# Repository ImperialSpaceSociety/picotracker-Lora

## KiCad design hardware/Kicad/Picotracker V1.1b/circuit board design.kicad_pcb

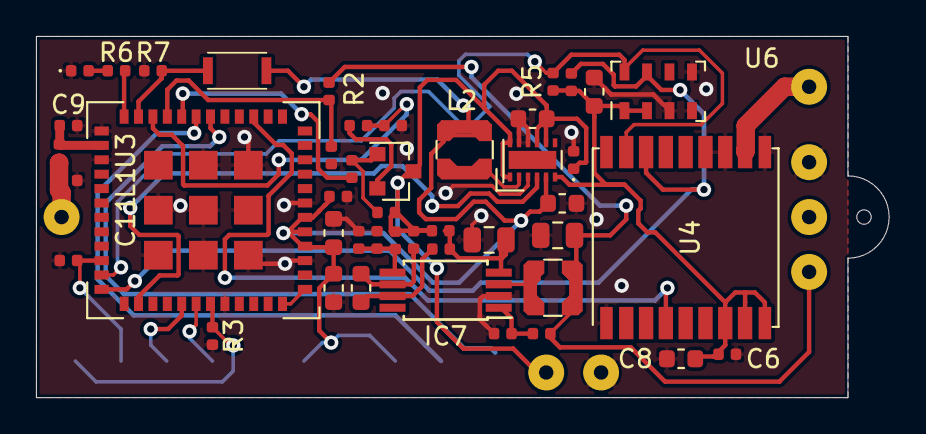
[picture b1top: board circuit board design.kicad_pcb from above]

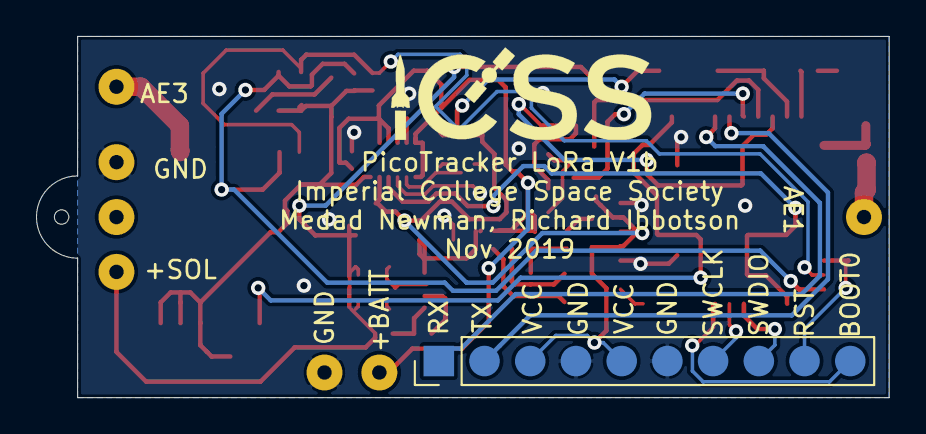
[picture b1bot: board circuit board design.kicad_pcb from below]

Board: 2 copper layers, 47.4 x 20.1 mm, 55 parts (8 on the bottom side), 34 nets.

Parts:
AE1: Lora Antenna; SolderWirePad_1x01_Drill0.8mm
AE3: GPS Antenna; SolderWirePad_1x01_Drill0.8mm
C1, C5, C6, C13: 100nF; C_0402_1005Metric
C2, C8, C10, C12: 10uF; C_0603_1608Metric
C3: 4.7uF; C_0805_2012Metric
C4, C16: 1nF; C_0402_1005Metric
C7, C15: 1uF; C_0603_1608Metric
C9, C11: NF; C_0402_1005Metric
C14: 220nF; C_0603_1608Metric
C17: 22uF; C_0805_2012Metric
D1: LED; LED_0402_1005Metric
D2: D_Schottky; D_0402_1005Metric
IC7: SPV1040; TSSOP-8_4.4x3mm_P0.65mm
J1: Conn_01x10; 10Pad
J2: GND; SolderWirePad_1x01_Drill0.8mm
J3: +SOL; SolderWirePad_1x01_Drill0.8mm
J4: BATT_V+; SolderWirePad_1x01_Drill0.8mm
J5: BATT_GND; SolderWirePad_1x01_Drill0.8mm
J6: ICSS LOGO; ICSS_Logo
L1: NF; C_0402_1005Metric
L2: 2.2uH; L_Coilcraft_LPS3015
L3: 10uH; L_Coilcraft_LPS3015
Q1: Q_PMOS_GSD; SOT-23
R1, R3: 10K; R_0402_1005Metric
R2, R7, R9, R15, R16: 100K; R_0402_1005Metric
R4, R5: 4.7K; R_0402_1005Metric
R6, R8, R10, R11: 1K; R_0402_1005Metric
R12: 1Ohm; R_0402_1005Metric
R13: 10M; R_0402_1005Metric
R14: 5.1M; R_0402_1005Metric
SW1: SW_Push; EVPAWCD4A
SolarCellMount1: Unconnected; SolderWirePad_1x01_Drill0.8mm
StringHole1: Unconnected; SolderWirePad_1x01_Drill0.8mm
U2: TPS62740; WSON-12-1EP_3x2mm_P0.5mm_EP1x2.65
U3: CMWX1ZZABZ-078; CMWX1ZZABZ
U4: MAX-M8C; ublox_MAX
U6: MS5607-02BA; LGA-8_3x5mm_P1.25mm

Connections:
+BATT: C2.1, D2.1, J4.1, Q1.3, R1.1, R11.1, R12.2, R13.2, U2.1, U2.8, U2.9, U2.12
+SOL: C3.1, J3.1, L3.2, R2.1, R8.1
/BATT_PWR_MEASURE: C13.2, U3.20
/BATT_VOLTS: R15.2, R16.1, U3.22
/BOOT0: J1.10, R3.1, U3.43
/GPS_TIMEPULSE: U3.15, U4.4
/I2C1_SCL: R5.2, U3.35, U4.17, U6.8
/I2C1_SDA: R4.2, U3.36, U4.16, U6.7
/LED: R6.2, U3.24
/RESET: C1.1, J1.9, U3.34
/SENSOR_EN: U2.4, U3.38
/SOLAR_VOLTS: R2.2, R9.1, U3.21
/SWCLK: J1.7, U3.42
/SWDIO: J1.8, U3.41
/SWITCH: R7.1, SW1.1, U3.23
/TCXO_EN: U3.1, U3.48
/USART1_RX: J1.1, U3.18
/USART1_TX: J1.2, U3.19
GND: C1.2, C2.2, C3.2, C4.2, C5.2, C6.2, C7.2, C8.2, C9.2, C10.2, C11.2, C12.2, C14.2, C16.2, C17.1, D1.1, D2.2, IC7.2, J1.4, J1.6, J2.1, J5.1, R3.2, R7.2, R9.2, R14.1, R16.2, U2.3, U2.10, U2.11, U3.3, U3.7, U3.25, U3.27, U3.44, U3.49, U3.50, U3.51, U3.52, U3.53, U3.54, U3.55, U3.56, U3.57, U4.1, U4.10, U4.12, U4.13, U6.3, U6.4, U6.5
unnamed: AE1.1, C11.1, L1.1
unnamed: AE3.1, U4.11
unnamed: C4.1, IC7.1, R8.2
unnamed: C9.1, L1.2, U3.26
unnamed: C13.1, Q1.1, R1.2
unnamed: C15.1, IC7.7, R10.2
unnamed: C15.2, IC7.6, R11.2
unnamed: C16.1, IC7.5, R13.1, R14.2
unnamed: C17.2, IC7.4, R10.1, R12.1
unnamed: D1.2, R6.1
unnamed: IC7.3, L3.1
unnamed: L2.2, U2.2
unnamed: Q1.2, R15.1
SENSOR_VCC: C6.1, C8.1, C14.1, R4.1, R5.1, U2.6, U4.7, U4.8, U4.9, U6.1, U6.2
VCC: C5.1, C7.1, C10.1, C12.1, J1.3, J1.5, L2.1, SW1.2, U2.5, U3.4, U3.5, U3.6

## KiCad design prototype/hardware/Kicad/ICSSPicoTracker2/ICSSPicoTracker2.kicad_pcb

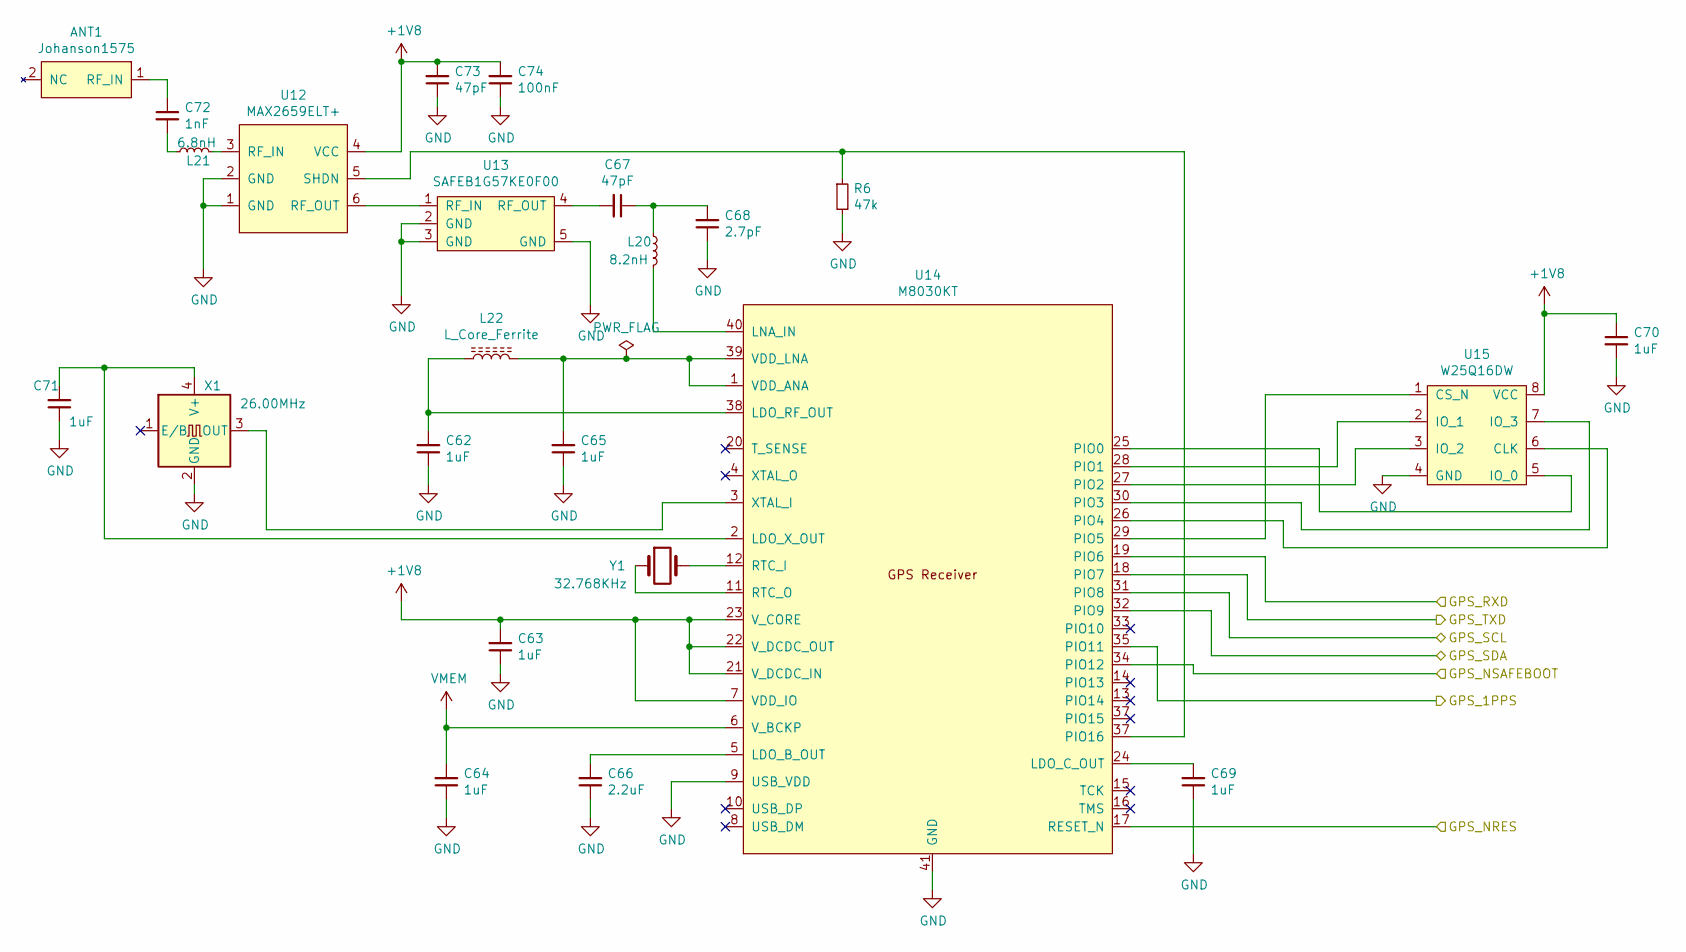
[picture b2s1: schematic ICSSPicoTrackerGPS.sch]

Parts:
ANT1: Johanson1575
C62, C63, C64, C65, C69, C70, C71: 1uF; C_0603_1608Metric
C66: 2.2uF; C_0603_1608Metric
C67, C73: 47pF; C_0402_1005Metric
C68: 2.7pF; C_0402_1005Metric
C72: 1nF; C_0402_1005Metric
C74: 100nF; C_0603_1608Metric
L20: 8.2nH; L_0402_1005Metric
L21: 6.8nH; L_0402_1005Metric
L22: L_Core_Ferrite; L_0603_1608Metric
R6: 47k; R_0603_1608Metric
U12: MAX2659ELT+; uDFN-6_1.0x1.5mm_P0.5mm
U13: SAFEB1G57KE0F00; Murata SAFE
U14: M8030KT; QFN-40-1EP_5x5mm_P0.4mm_EP3.6x3.6mm_ThermalVias
U15: W25Q16DW; WSON-8-1EP_6x5mm_P1.27mm_EP3.4x4.3mm
X1: 26.00MHz; Oscillator_SMD_IQD_IQXO70-4Pin_7.5x5.0mm
Y1: 32.768KHz; Crystal_SMD_2012-2Pin_2.0x1.2mm

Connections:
+1V8: C63.2, C70.1, C73.2, C74.2, U12.4 (VCC), U14.7 (VDD_IO), U14.21 (V_DCDC_IN), U14.22 (V_DCDC_OUT), U14.23 (V_CORE), U15.8 (VCC); also elsewhere on the board
/GPS/GPS_1PPS: U14.35 (PIO11); also elsewhere on the board
/GPS/GPS_NRES: U14.17 (RESET_N); also elsewhere on the board
/GPS/GPS_NSAFEBOOT: U14.34 (PIO12); also elsewhere on the board
/GPS/GPS_RXD: U14.19 (PIO6); also elsewhere on the board
/GPS/GPS_SCL: U14.31 (PIO8); also elsewhere on the board
/GPS/GPS_SDA: U14.32 (PIO9); also elsewhere on the board
/GPS/GPS_TXD: U14.18 (PIO7); also elsewhere on the board
GND: C62.1, C63.1, C64.1, C65.1, C66.1, C68.1, C69.1, C70.2, C71.1, C73.1, C74.1, R6.2, U12.1 (GND), U12.2 (GND), U13.2 (GND), U13.3 (GND), U13.5 (GND), U14.9 (USB_VDD), U14.41 (GND), U15.4 (GND), X1.2 (GND); also elsewhere on the board
unnamed: ANT1.1 (RF_IN), C72.1
unnamed: C62.2, L22.1, U14.38 (LDO_RF_OUT)
unnamed: C65.2, L22.2, U14.1 (VDD_ANA), U14.39 (VDD_LNA)
unnamed: C66.2, U14.5 (LDO_B_OUT)
unnamed: C67.1, C68.2, L20.1
unnamed: C67.2, U13.4 (RF_OUT)
unnamed: C69.2, U14.24 (LDO_C_OUT)
unnamed: C71.2, U14.2 (LDO_X_OUT), X1.4 (V+)
unnamed: C72.2, L21.2
unnamed: L20.2, U14.40 (LNA_IN)
unnamed: L21.1, U12.3 (RF_IN)
unnamed: U12.6 (RF_OUT), U13.1 (RF_IN)
unnamed: U14.3 (XTAL_I), X1.3 (OUT)
unnamed: U14.11 (RTC_O), Y1.1
unnamed: U14.12 (RTC_I), Y1.2
unnamed: U14.25 (PIO0), U15.5 (IO_0)
unnamed: U14.26 (PIO4), U15.6 (CLK)
unnamed: U14.27 (PIO2), U15.3 (IO_2)
unnamed: U14.28 (PIO1), U15.2 (IO_1)
unnamed: U14.29 (PIO5), U15.1 (CS_N)
unnamed: U14.30 (PIO3), U15.7 (IO_3)
VMEM: C64.2, U14.6 (V_BCKP); also elsewhere on the board

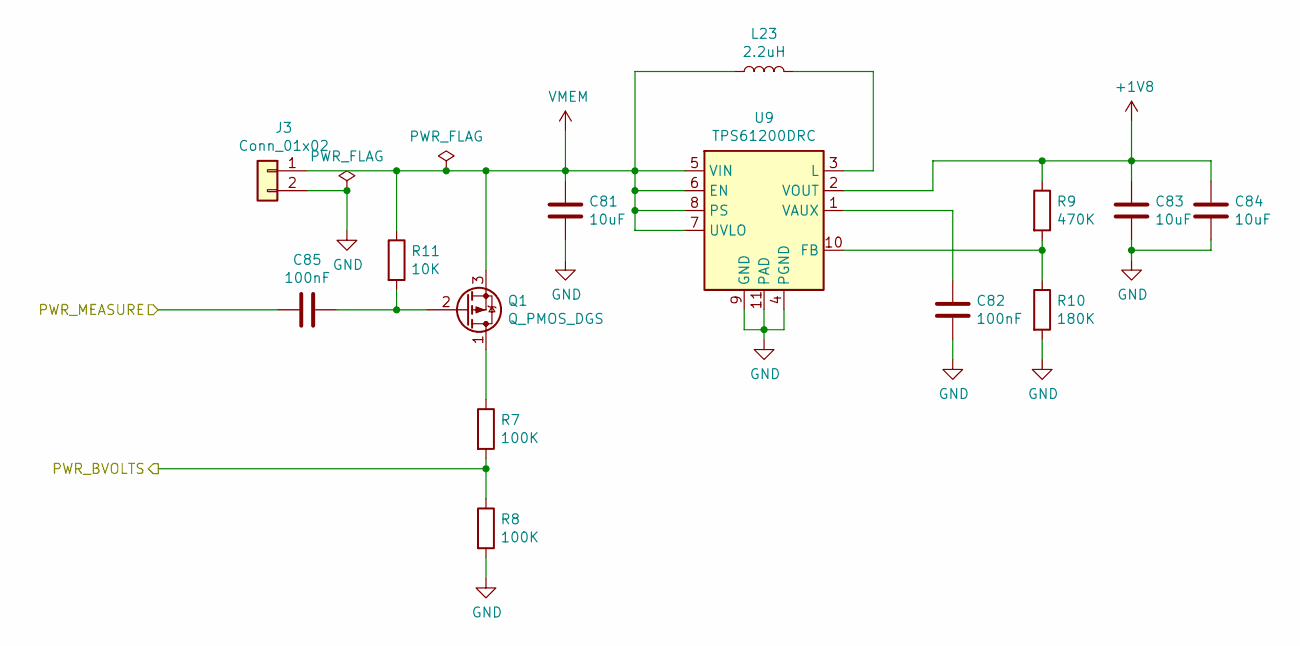
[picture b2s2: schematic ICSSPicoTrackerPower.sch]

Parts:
C81, C83, C84: 10uF; C_0603_1608Metric
C82, C85: 100nF; C_0603_1608Metric
J3: Conn_01x02; PinHeader_1x02_P1.00mm_Vertical
L23: 2.2uH; L_Taiyo-Yuden_NR-30xx
Q1: Q_PMOS_DGS; SOT-23
R7, R8: 100K; R_0603_1608Metric
R9: 470K; R_0603_1608Metric
R10: 180K; R_0603_1608Metric
R11: 10K; R_0603_1608Metric
U9: TPS61200DRC; Texas_S-PVSON-N10_ThermalVias

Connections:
+1V8: C83.1, C84.1, R9.1, U9.2 (VOUT); also elsewhere on the board
/MCU/MCU_PA02: R7.2, R8.1; also elsewhere on the board
/MCU/MCU_PA13: C85.1; also elsewhere on the board
GND: C81.2, C82.2, C83.2, C84.2, J3.2, R8.2, R10.2, U9.4 (PGND), U9.9 (GND), U9.11 (PAD); also elsewhere on the board
unnamed: C82.1, U9.1 (VAUX)
unnamed: C85.2, Q1.2 (G), R11.2
unnamed: L23.2, U9.3 (L)
unnamed: Q1.1 (D), R7.1
unnamed: R9.2, R10.1, U9.10 (FB)
VMEM: C81.1, J3.1, L23.1, Q1.3 (S), R11.1, U9.5 (VIN), U9.6 (EN), U9.7 (UVLO), U9.8 (PS); also elsewhere on the board

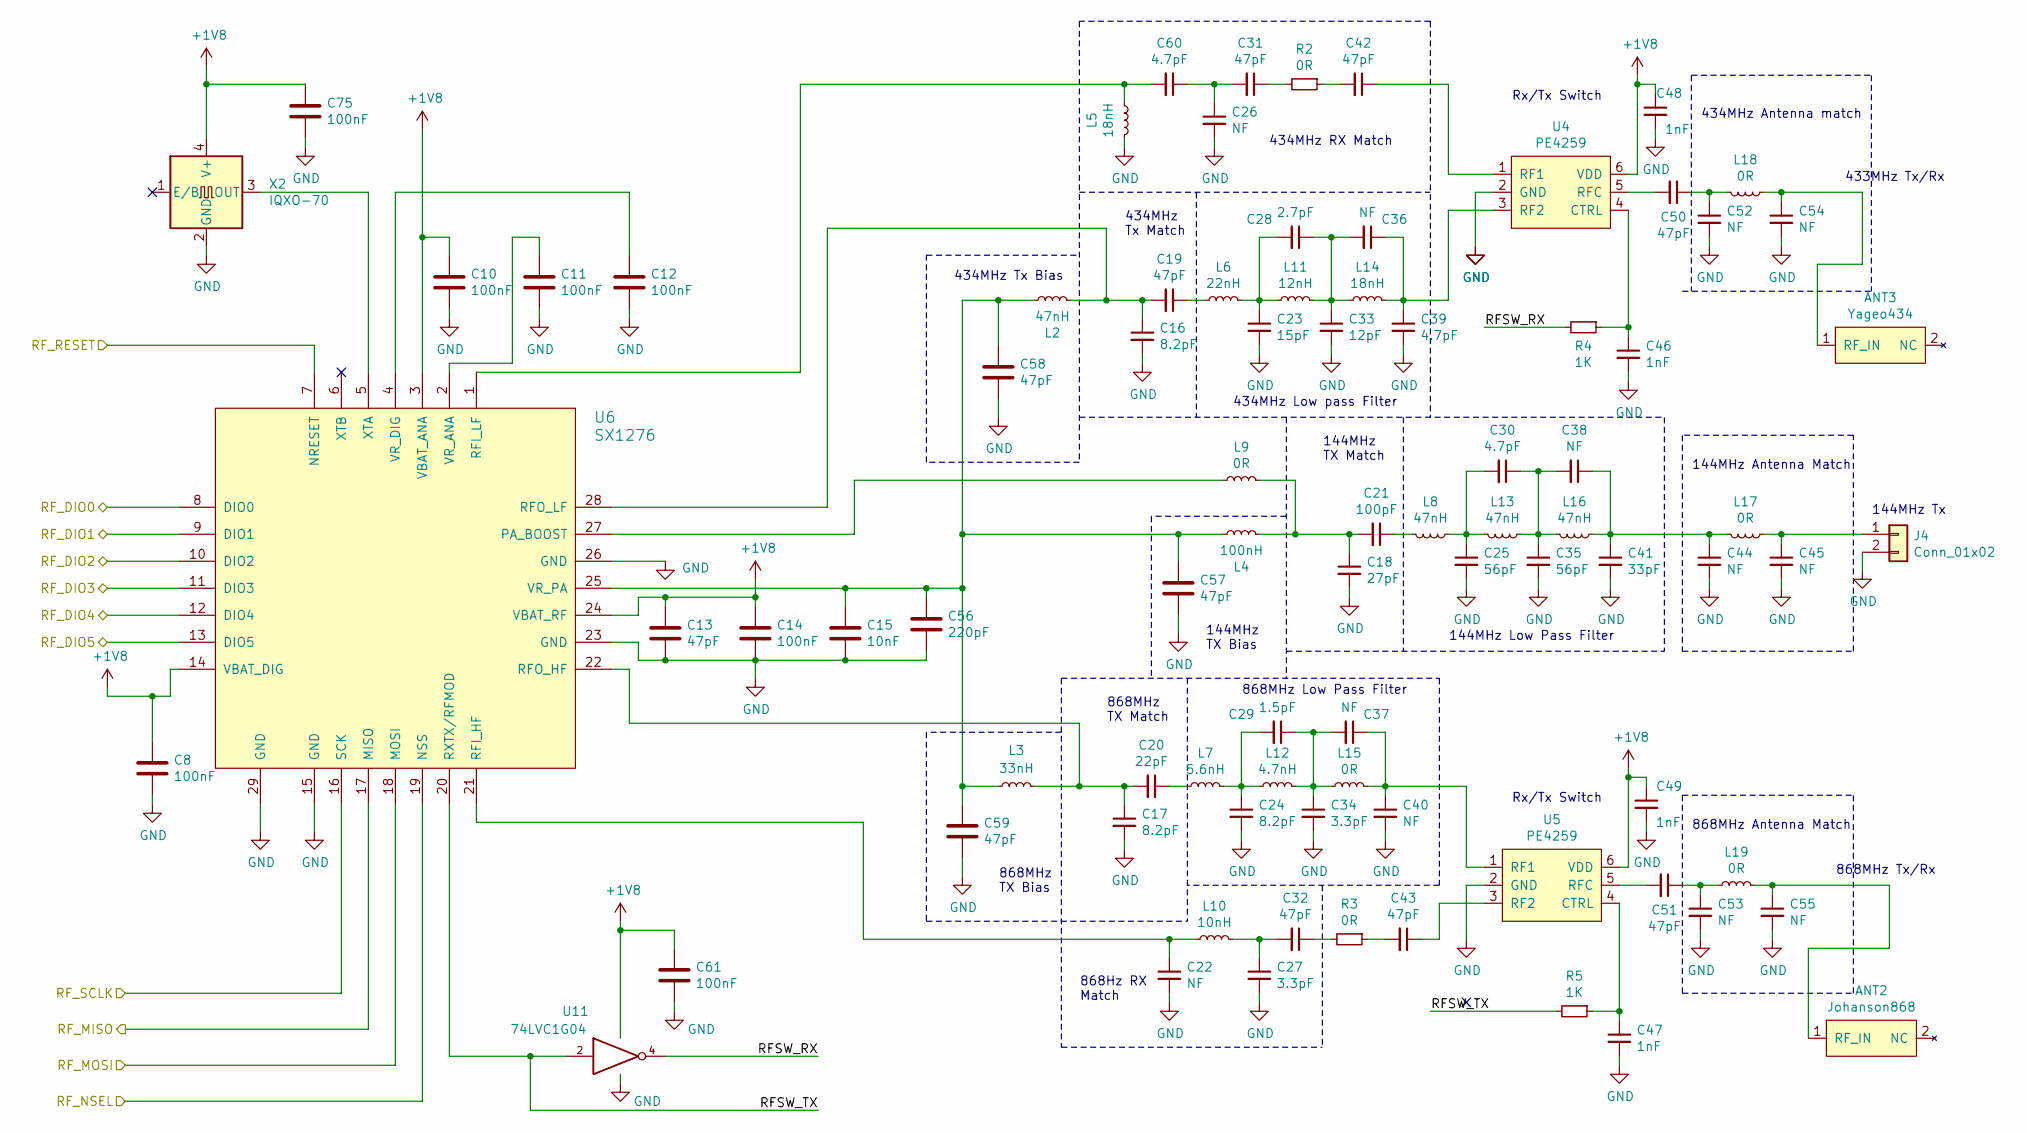
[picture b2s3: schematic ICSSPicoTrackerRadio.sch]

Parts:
ANT2: Johanson868
ANT3: Yageo434
C8, C10, C11, C12, C14, C61, C75: 100nF; C_0603_1608Metric
C13, C19, C31, C32, C42, C43, C50, C51, C57, C58, C59: 47pF; C_0402_1005Metric
C15: 10nF; C_0402_1005Metric
C16, C17, C24: 8.2pF; C_0402_1005Metric
C18: 27pF; C_0402_1005Metric
C20: 22pF; C_0402_1005Metric
C21: 100pF; C_0402_1005Metric
C22, C26, C36, C37, C38, C40, C44, C45, C52, C53, C54, C55: NF; C_0402_1005Metric
C23: 15pF; C_0402_1005Metric
C25, C35: 56pF; C_0402_1005Metric
C27, C34: 3.3pF; C_0402_1005Metric
C28: 2.7pF; C_0402_1005Metric
C29: 1.5pF; C_0402_1005Metric
C30, C39, C60: 4.7pF; C_0402_1005Metric
C33: 12pF; C_0402_1005Metric
C41: 33pF; C_0402_1005Metric
C46, C47, C48, C49: 1nF; C_0402_1005Metric
C56: 220pF; C_0402_1005Metric
J4: Conn_01x02; PinHeader_1x02_P2.54mm_Vertical
L2, L8, L13, L16: 47nH; L_0402_1005Metric
L3: 33nH; L_0402_1005Metric
L4: 100nH; L_0402_1005Metric
L5, L14: 18nH; L_0402_1005Metric
L6: 22nH; L_0402_1005Metric
L7: 5.6nH; L_0402_1005Metric
L9, L15, L17, L18, L19: 0R; L_0402_1005Metric
L10: 10nH; L_0402_1005Metric
L11: 12nH; L_0402_1005Metric
L12: 4.7nH; L_0402_1005Metric
R2, R3: 0R; R_0603_1608Metric
R4, R5: 1K; R_0603_1608Metric
U4, U5: PE4259; SOT-363_SC-70-6_Handsoldering
U6: SX1276; QFN-28-1EP_6x6mm_P0.65mm_EP4.25x4.25mm_ThermalVias
U11: 74LVC1G04; SOT-353_SC-70-5
X2: IQXO-70; Oscillator_SMD_SeikoEpson_SG210-4Pin_2.5x2.0mm

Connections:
+1V8: C8.1, C10.1, C13.1, C14.1, C48.1, C49.1, C61.1, C75.1, U4.6 (VDD), U5.6 (VDD), U6.3 (VBAT_ANA), U6.14 (VBAT_DIG), U6.24 (VBAT_RF), U11.5 (VCC), X2.4 (V+); also elsewhere on the board
/MCU/MCU_MISO1: U6.17 (MISO); also elsewhere on the board
/MCU/MCU_MOSI1: U6.18 (MOSI); also elsewhere on the board
/MCU/MCU_NSEL1: U6.19 (NSS); also elsewhere on the board
/MCU/MCU_PA03: U6.13 (DIO5); also elsewhere on the board
/MCU/MCU_PA04: U6.12 (DIO4); also elsewhere on the board
/MCU/MCU_PA05: U6.11 (DIO3); also elsewhere on the board
/MCU/MCU_PA06: U6.10 (DIO2); also elsewhere on the board
/MCU/MCU_PA07: U6.9 (DIO1); also elsewhere on the board
/MCU/MCU_PA08: U6.8 (DIO0); also elsewhere on the board
/MCU/MCU_PA09: U6.7 (NRESET); also elsewhere on the board
/MCU/MCU_SCLK1: U6.16 (SCK); also elsewhere on the board
/Telemetry Radio/RFSW_RX: R4.2, U11.4
/Telemetry Radio/RFSW_TX: R5.2, U6.20 (RXTX/RFMOD), U11.2
GND: C8.2, C10.2, C11.2, C12.2, C13.2, C14.2, C15.2, C16.2, C17.2, C18.2, C22.2, C23.2, C24.2, C25.2, C26.2, C27.2, C33.2, C34.2, C35.2, C39.2, C40.2, C41.2, C44.2, C45.2, C46.2, C47.2, C48.2, C49.2, C52.2, C53.2, C54.2, C55.2, C56.2, C57.2, C58.2, C59.2, C61.2, C75.2, J4.2, L5.2, U4.2 (GND), U5.2 (GND), U6.15 (GND), U6.23 (GND), U6.26 (GND), U6.29 (GND), U11.3 (GND), X2.2 (GND); also elsewhere on the board
unnamed: ANT2.1 (RF_IN), C55.1, L19.2
unnamed: ANT3.1 (RF_IN), C54.1, L18.2
unnamed: C11.1, U6.2 (VR_ANA)
unnamed: C12.1, U6.4 (VR_DIG)
unnamed: C15.1, C56.1, C57.1, C58.1, C59.1, L2.1, L3.1, L4.1, U6.25 (VR_PA)
unnamed: C16.1, C19.2, L2.2, U6.28 (RFO_LF)
unnamed: C17.1, C20.2, L3.2, U6.22 (RFO_HF)
unnamed: C18.1, C21.2, L4.2, L9.2
unnamed: C19.1, L6.1
unnamed: C20.1, L7.1
unnamed: C21.1, L8.1
unnamed: C22.1, L10.1, U6.21 (RFI_HF)
unnamed: C23.1, C28.2, L6.2, L11.1
unnamed: C24.1, C29.2, L7.2, L12.1
unnamed: C25.1, C30.2, L8.2, L13.1
unnamed: C26.1, C31.2, C60.1
unnamed: C27.1, C32.2, L10.2
unnamed: C28.1, C33.1, C36.2, L11.2, L14.1
unnamed: C29.1, C34.1, C37.2, L12.2, L15.1
unnamed: C30.1, C35.1, C38.2, L13.2, L16.1
unnamed: C31.1, R2.2
unnamed: C32.1, R3.2
unnamed: C36.1, C39.1, L14.2, U4.3 (RF2)
unnamed: C37.1, C40.1, L15.2, U5.1 (RF1)
unnamed: C38.1, C41.1, C44.1, L16.2, L17.2
unnamed: C42.1, U4.1 (RF1)
unnamed: C42.2, R2.1
unnamed: C43.1, U5.3 (RF2)
unnamed: C43.2, R3.1
unnamed: C45.1, J4.1, L17.1
unnamed: C46.1, R4.1, U4.4 (CTRL)
unnamed: C47.1, R5.1, U5.4 (CTRL)
unnamed: C50.1, C52.1, L18.1
unnamed: C50.2, U4.5 (RFC)
unnamed: C51.1, C53.1, L19.1
unnamed: C51.2, U5.5 (RFC)
unnamed: C60.2, L5.1, U6.1 (RFI_LF)
unnamed: L9.1, U6.27 (PA_BOOST)
unnamed: U6.5 (XTA), X2.3 (OUT)

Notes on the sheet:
144MHz Tx
433MHz Tx/Rx
868MHz Tx/Rx
144MHz Low Pass Filter
144MHz Antenna Match
144MHz TX Bias
144MHz TX Match
Rx/Tx Switch
868MHz TX Bias
868MHz TX Match
868MHz Low Pass Filter
868MHz Antenna Match
434MHz RX Match
434MHz Tx Bias
434MHz Tx Match
434MHz Low pass Filter
434MHz Antenna match
868Hz RX Match

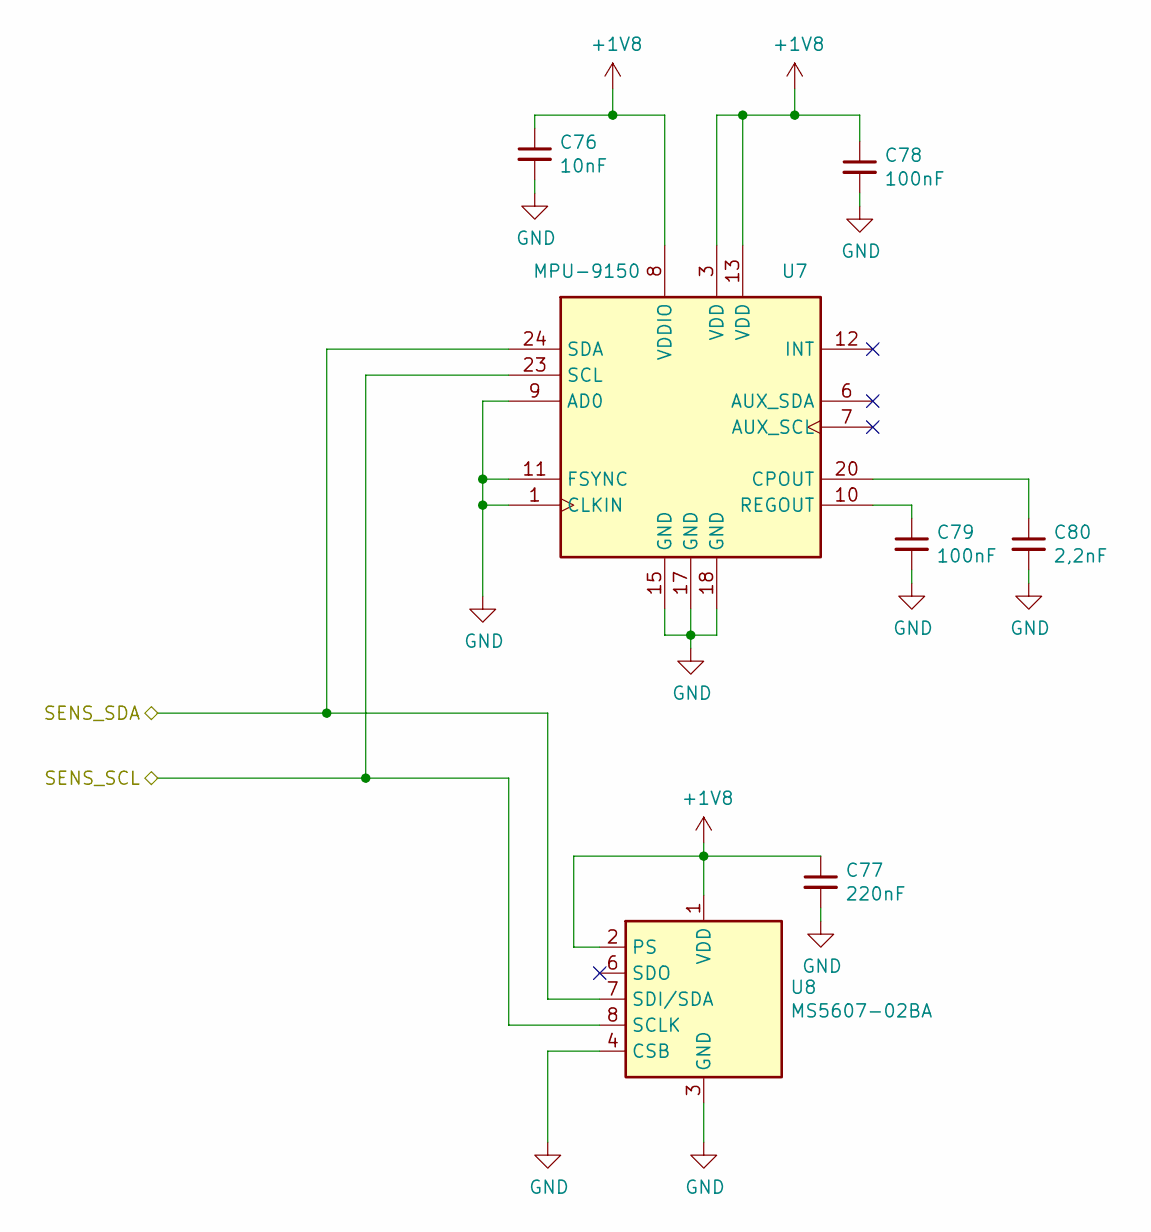
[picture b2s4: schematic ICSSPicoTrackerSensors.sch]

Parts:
C76: 10nF; C_0402_1005Metric
C77: 220nF; C_0402_1005Metric
C78, C79: 100nF; C_0603_1608Metric
C80: 2,2nF; C_0402_1005Metric
U7: MPU-9150; InvenSense_QFN-24_4x4mm_P0.5mm
U8: MS5607-02BA; LGA-8_3x5mm_P1.25mm

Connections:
+1V8: C76.1, C77.1, C78.1, U7.3 (VDD), U7.8 (VDDIO), U7.13 (VDD), U8.1 (VDD), U8.2 (PS); also elsewhere on the board
/GPS/GPS_SCL: U7.23 (SCL), U8.8 (SCLK); also elsewhere on the board
/GPS/GPS_SDA: U7.24 (SDA), U8.7 (SDI/SDA); also elsewhere on the board
GND: C76.2, C77.2, C78.2, C79.2, C80.2, U7.1 (CLKIN), U7.9 (AD0), U7.11 (FSYNC), U7.15 (GND), U7.17 (GND), U7.18 (GND), U8.3 (GND), U8.4 (CSB), U8.5 (CSB); also elsewhere on the board
unnamed: C79.1, U7.10 (REGOUT)
unnamed: C80.1, U7.20 (CPOUT)

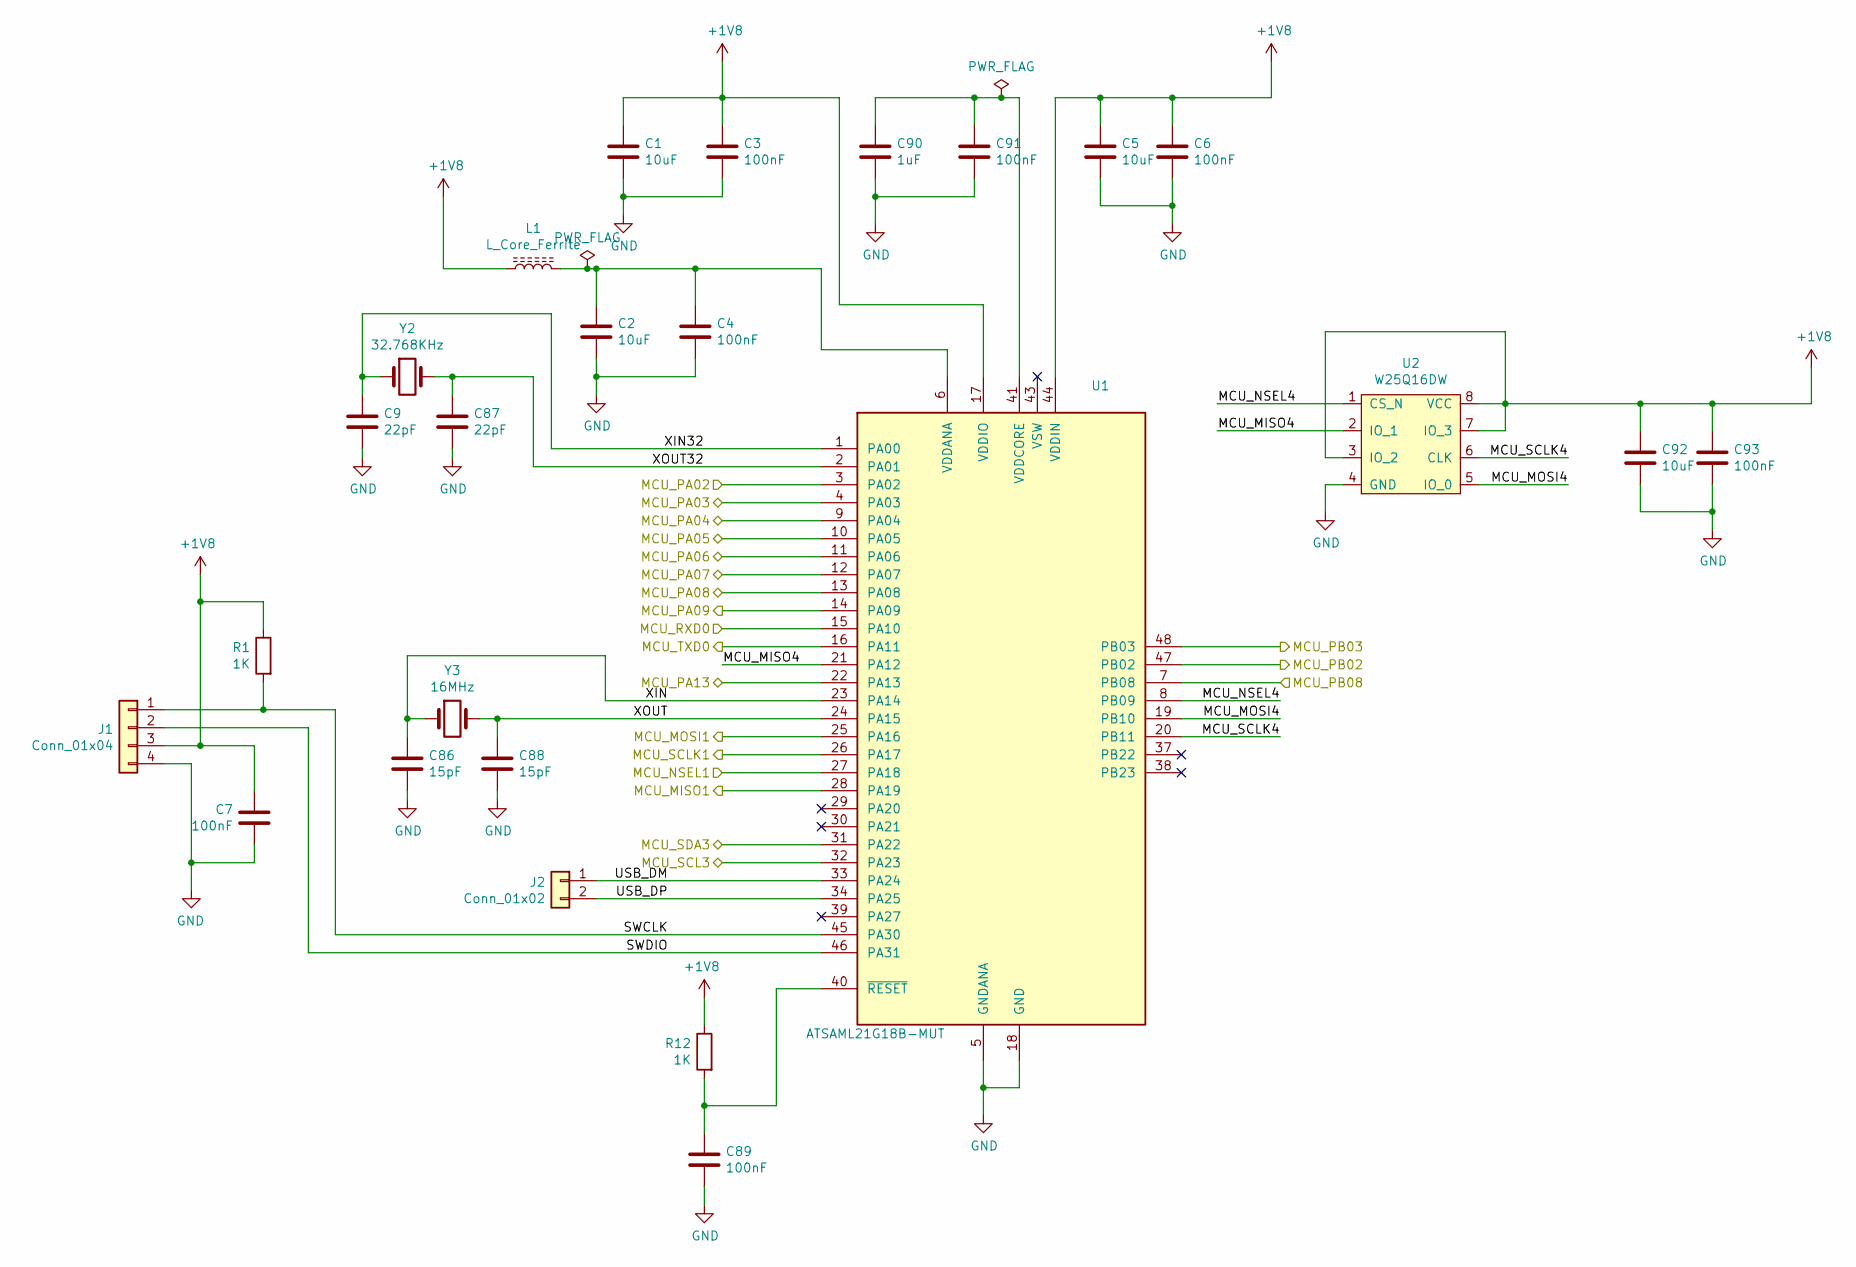
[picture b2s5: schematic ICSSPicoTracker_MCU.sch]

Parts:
C1, C2, C5, C92: 10uF; C_0603_1608Metric
C3, C4, C6, C7, C89, C91, C93: 100nF; C_0603_1608Metric
C9, C87: 22pF; C_0402_1005Metric
C86, C88: 15pF; C_0402_1005Metric
C90: 1uF; C_0603_1608Metric
J1: Conn_01x04; PinHeader_1x04_P1.00mm_Vertical
J2: Conn_01x02; PinHeader_1x02_P1.00mm_Vertical
L1: L_Core_Ferrite; L_0603_1608Metric
R1, R12: 1K; R_0603_1608Metric
U1: ATSAML21G18B-MUT; QFN-48-1EP_7x7mm_P0.5mm_EP5.15x5.15mm
U2: W25Q16DW; WSON-8-1EP_6x5mm_P1.27mm_EP3.4x4.3mm
Y2: 32.768KHz; Crystal_SMD_2012-2Pin_2.0x1.2mm
Y3: 16MHz; Crystal_SMD_2520-4Pin_2.5x2.0mm

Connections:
+1V8: C1.1, C3.1, C5.1, C6.1, C7.1, C92.1, C93.1, J1.3, L1.1, R1.1, R12.1, U1.17 (VDDIO), U1.36 (VDDIO), U1.44 (VDDIN), U2.3 (IO_2), U2.7 (IO_3), U2.8 (VCC); also elsewhere on the board
/GPS/GPS_1PPS: U1.7 (PB08); also elsewhere on the board
/GPS/GPS_NRES: U1.47 (PB02); also elsewhere on the board
/GPS/GPS_NSAFEBOOT: U1.48 (PB03); also elsewhere on the board
/GPS/GPS_RXD: U1.16 (PA11); also elsewhere on the board
/GPS/GPS_SCL: U1.32 (PA23); also elsewhere on the board
/GPS/GPS_SDA: U1.31 (PA22); also elsewhere on the board
/GPS/GPS_TXD: U1.15 (PA10); also elsewhere on the board
/MCU/MCU_MISO1: U1.28 (PA19); also elsewhere on the board
/MCU/MCU_MISO4: U1.21 (PA12), U2.2 (IO_1)
/MCU/MCU_MOSI1: U1.25 (PA16); also elsewhere on the board
/MCU/MCU_MOSI4: U1.19 (PB10), U2.5 (IO_0)
/MCU/MCU_NSEL1: U1.27 (PA18); also elsewhere on the board
/MCU/MCU_NSEL4: U1.8 (PB09), U2.1 (CS_N)
/MCU/MCU_PA02: U1.3 (PA02); also elsewhere on the board
/MCU/MCU_PA03: U1.4 (PA03); also elsewhere on the board
/MCU/MCU_PA04: U1.9 (PA04); also elsewhere on the board
/MCU/MCU_PA05: U1.10 (PA05); also elsewhere on the board
/MCU/MCU_PA06: U1.11 (PA06); also elsewhere on the board
/MCU/MCU_PA07: U1.12 (PA07); also elsewhere on the board
/MCU/MCU_PA08: U1.13 (PA08); also elsewhere on the board
/MCU/MCU_PA09: U1.14 (PA09); also elsewhere on the board
/MCU/MCU_PA13: U1.22 (PA13); also elsewhere on the board
/MCU/MCU_SCLK1: U1.26 (PA17); also elsewhere on the board
/MCU/MCU_SCLK4: U1.20 (PB11), U2.6 (CLK)
/MCU/SWCLK: J1.1, R1.2, U1.45 (PA30)
/MCU/SWDIO: J1.2, U1.46 (PA31)
/MCU/USB_DM: J2.1, U1.33 (PA24)
/MCU/USB_DP: J2.2, U1.34 (PA25)
/MCU/XIN: C86.1, U1.23 (PA14), Y3.1
/MCU/XIN32: C9.1, U1.1 (PA00), Y2.1
/MCU/XOUT: C88.1, U1.24 (PA15), Y3.2
/MCU/XOUT32: C87.1, U1.2 (PA01), Y2.2
GND: C1.2, C2.2, C3.2, C4.2, C5.2, C6.2, C7.2, C9.2, C86.2, C87.2, C88.2, C89.2, C90.2, C91.2, C92.2, C93.2, J1.4, U1.5 (GNDANA), U1.18 (GND), U1.35 (GND), U1.42 (GND), U2.4 (GND); also elsewhere on the board
unnamed: C2.1, C4.1, L1.2, U1.6 (VDDANA)
unnamed: C89.1, R12.2, U1.40 (~RESET)
unnamed: C90.1, C91.1, U1.41 (VDDCORE)

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
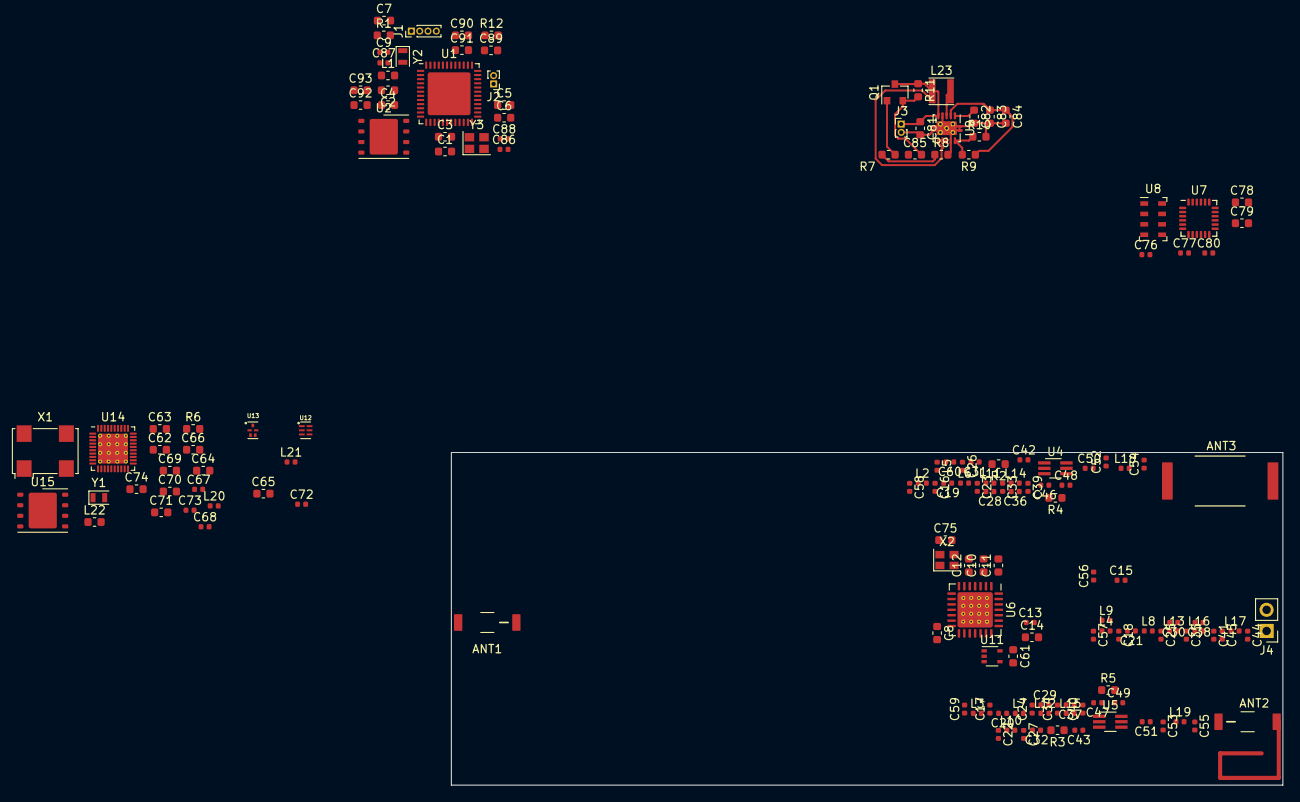
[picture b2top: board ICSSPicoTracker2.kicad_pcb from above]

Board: 4 copper layers, 100.0 x 40.0 mm, 154 parts (0 on the bottom side), 108 nets.
